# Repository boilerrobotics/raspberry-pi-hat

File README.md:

# RaspberryPi-Hat

Please update this readme.
Please make a KiCAD project, then update the PROJECT_NAME at the top of the pcb_image.yaml (inside the .github/workflows folder)

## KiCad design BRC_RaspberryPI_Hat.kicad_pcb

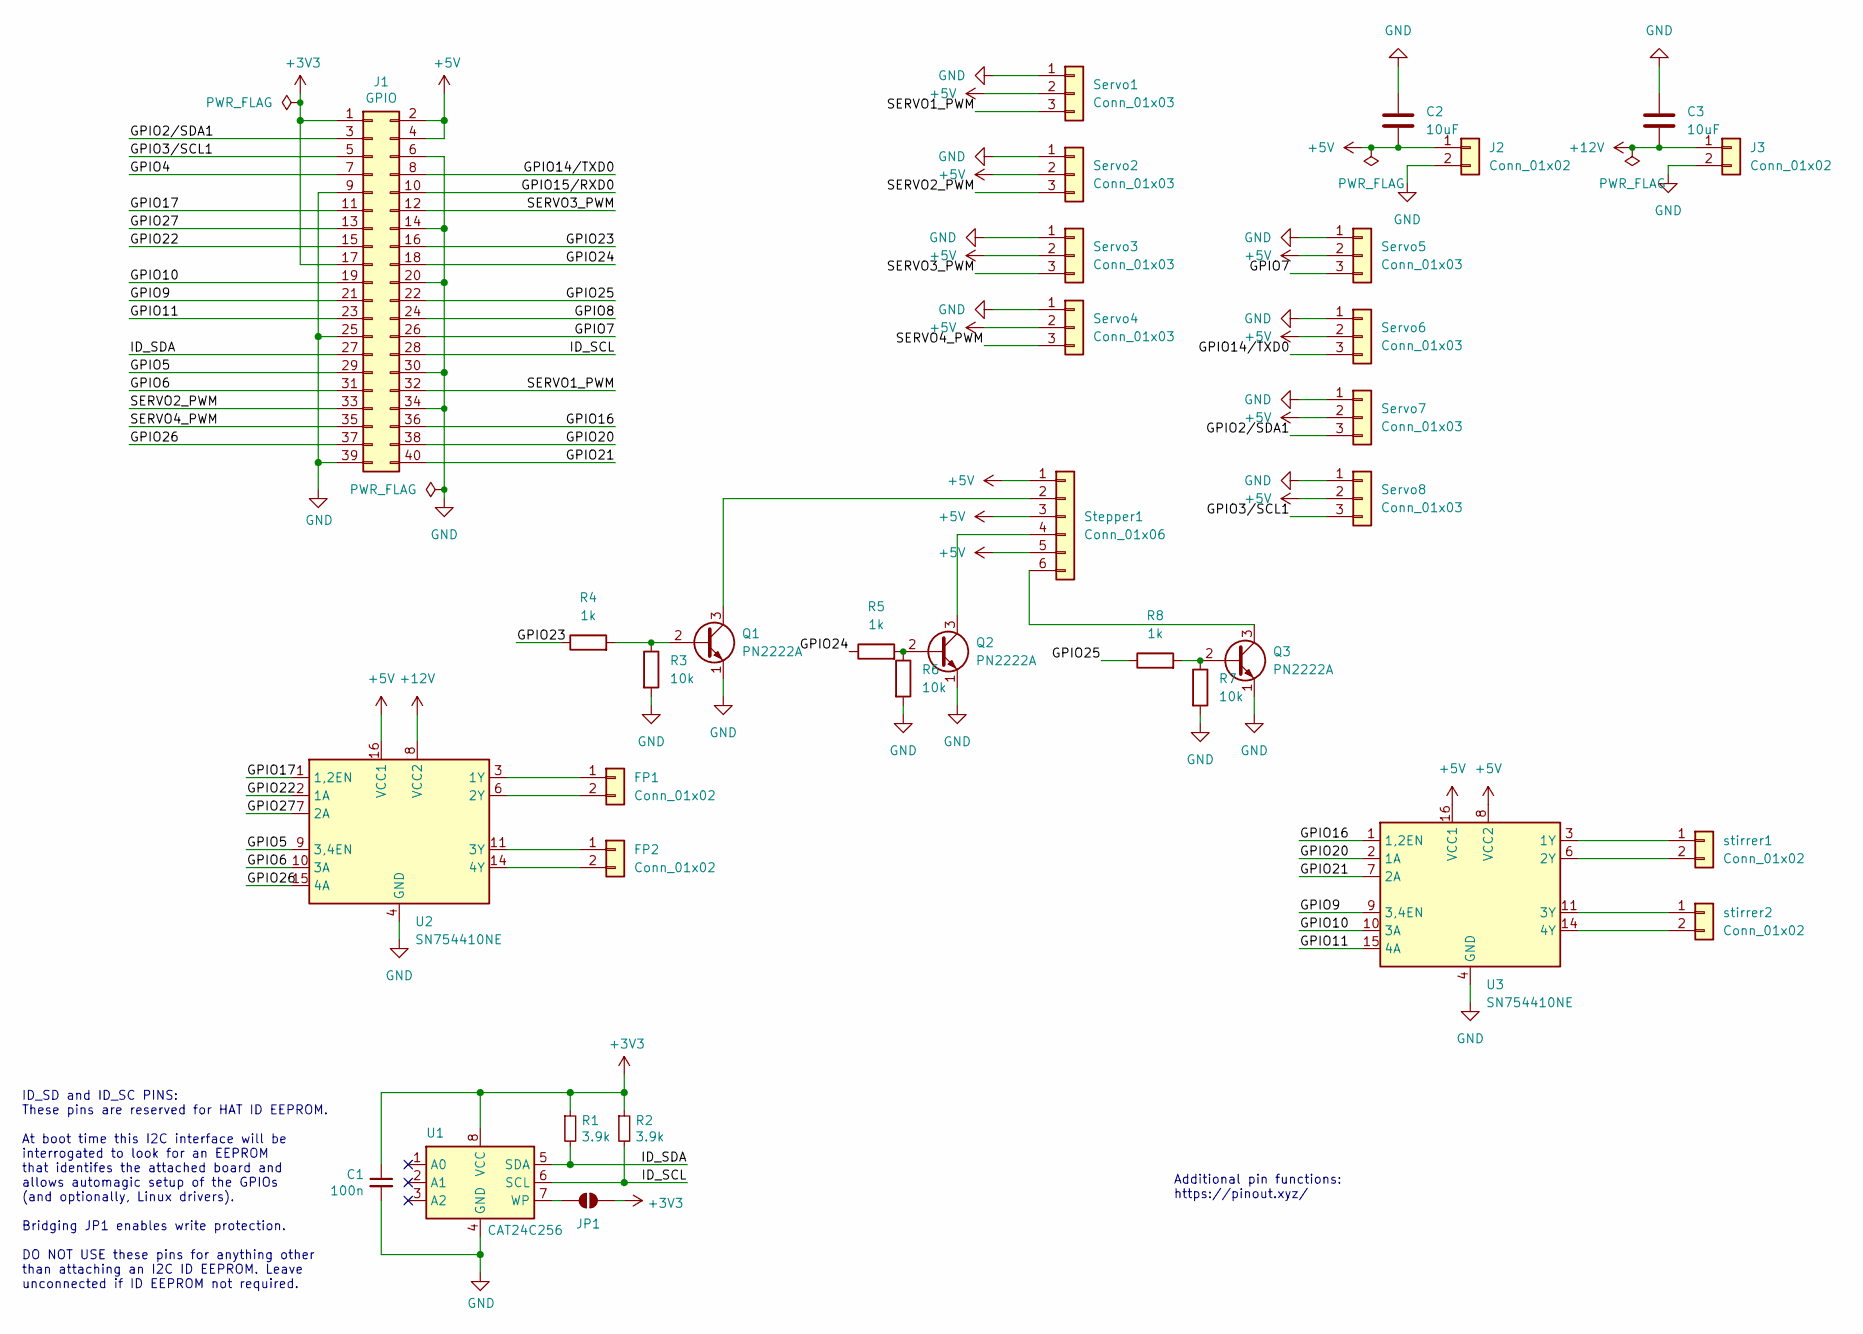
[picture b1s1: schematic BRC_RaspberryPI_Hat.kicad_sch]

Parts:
C1: 100n; C_Disc_D5.0mm_W2.5mm_P2.50mm
C2, C3: 10uF; C_0805_2012Metric
FP1, FP2: Conn_01x02; JST_XH_B2B-XH-A_1x02_P2.50mm_Vertical
J1: GPIO; PinSocket_2x20_P2.54mm_Vertical
J2, J3: Conn_01x02; AMASS_XT60-F_1x02_P7.20mm_Vertical
JP1: ID_WP
Q1, Q2, Q3: PN2222A; TO-92_Inline
R1, R2: 3.9k; R_Axial_DIN0207_L6.3mm_D2.5mm_P7.62mm_Horizontal
R3, R6, R7: 10k; R_Axial_DIN0207_L6.3mm_D2.5mm_P7.62mm_Horizontal
R4, R5, R8: 1k; R_Axial_DIN0207_L6.3mm_D2.5mm_P7.62mm_Horizontal
Servo1, Servo2, Servo3, Servo4, Servo5, Servo6, Servo7, Servo8: Conn_01x03; PinHeader_1x03_P2.54mm_Vertical
Stepper1: Conn_01x06; PinHeader_1x06_P2.54mm_Vertical
U1: CAT24C256
U2, U3: SN754410NE; DIP-16_W7.62mm
stirrer1, stirrer2: Conn_01x02; PinHeader_1x02_P2.54mm_Vertical

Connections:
+3V3: C1.1, J1.1, J1.17, JP1.2 (B), R1.1, R2.1, U1.8 (VCC)
+5V: C2.2, J1.2, J1.4, J2.1, Servo1.2, Servo2.2, Servo3.2, Servo4.2, Servo5.2, Servo6.2, Servo7.2, Servo8.2, Stepper1.1, Stepper1.3, Stepper1.5, U2.16 (VCC1), U3.8 (VCC2), U3.16 (VCC1)
+12V: C3.2, J3.1, U2.8 (VCC2)
/GPIO2/SDA1: J1.3, Servo7.3
/GPIO3/SCL1: J1.5, Servo8.3
/GPIO4: J1.7
/GPIO5: J1.29, U2.9 (3,4EN)
/GPIO6: J1.31, U2.10 (3A)
/GPIO7: J1.26, Servo5.3
/GPIO8: J1.24
/GPIO9: J1.21, U3.9 (3,4EN)
/GPIO10: J1.19, U3.10 (3A)
/GPIO11: J1.23, U3.15 (4A)
/GPIO14/TXD0: J1.8, Servo6.3
/GPIO15/RXD0: J1.10
/GPIO16: J1.36, U3.1 (1,2EN)
/GPIO17: J1.11, U2.1 (1,2EN)
/GPIO20: J1.38, U3.2 (1A)
/GPIO21: J1.40, U3.7 (2A)
/GPIO22: J1.15, U2.2 (1A)
/GPIO23: J1.16, R4.1
/GPIO24: J1.18, R5.1
/GPIO25: J1.22, R8.1
/GPIO26: J1.37, U2.15 (4A)
/GPIO27: J1.13, U2.7 (2A)
/ID_SCL: J1.28, R2.2, U1.6 (SCL)
/ID_SDA: J1.27, R1.2, U1.5 (SDA)
/SERVO1_PWM: J1.32, Servo1.3
/SERVO2_PWM: J1.33, Servo2.3
/SERVO3_PWM: J1.12, Servo3.3
/SERVO4_PWM: J1.35, Servo4.3
GND: C1.2, C2.1, C3.1, J1.6, J1.9, J1.14, J1.20, J1.25, J1.30, J1.34, J1.39, J2.2, J3.2, Q1.1 (E), Q2.1 (E), Q3.1 (E), R3.2, R6.2, R7.2, Servo1.1, Servo2.1, Servo3.1, Servo4.1, Servo5.1, Servo6.1, Servo7.1, Servo8.1, U1.4 (GND), U2.4 (GND), U2.5 (GND), U2.12 (GND), U2.13 (GND), U3.4 (GND), U3.5 (GND), U3.12 (GND), U3.13 (GND)
unnamed: FP1.1, U2.3 (1Y)
unnamed: FP1.2, U2.6 (2Y)
unnamed: FP2.1, U2.11 (3Y)
unnamed: FP2.2, U2.14 (4Y)
unnamed: JP1.1 (A), U1.7 (WP)
unnamed: Q1.2 (B), R3.1, R4.2
unnamed: Q1.3 (C), Stepper1.2
unnamed: Q2.2 (B), R5.2, R6.1
unnamed: Q2.3 (C), Stepper1.4
unnamed: Q3.2 (B), R7.1, R8.2
unnamed: Q3.3 (C), Stepper1.6
unnamed: U3.3 (1Y), stirrer1.1
unnamed: U3.6 (2Y), stirrer1.2
unnamed: U3.11 (3Y), stirrer2.1
unnamed: U3.14 (4Y), stirrer2.2

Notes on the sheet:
Additional pin functions: https://pinout.xyz/
ID_SD and ID_SC PINS: These pins are reserved for HAT ID EEPROM. At boot time this I2C interface will be interrogated to look for an EEPROM that identifes the attached board and allows automagic setup of the GPIOs (and optionally, Linux drivers). Bridging JP1 enables write protection. DO NOT USE th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

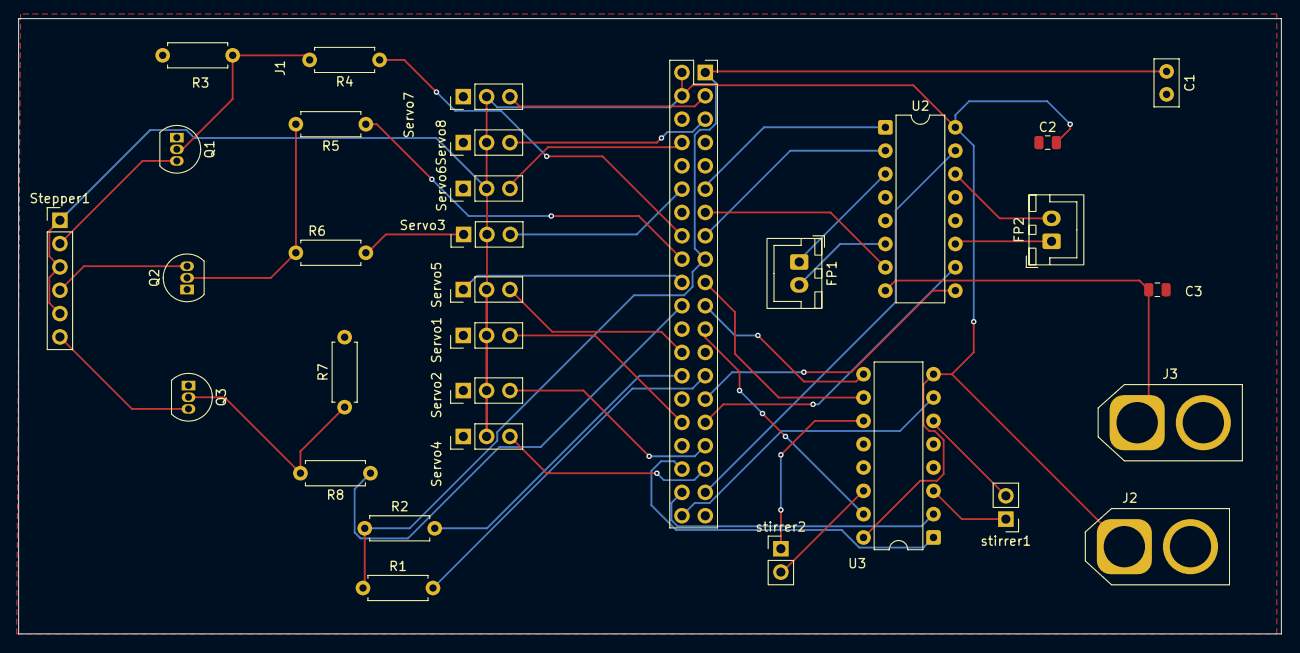
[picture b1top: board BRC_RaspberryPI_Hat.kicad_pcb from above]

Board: 2 copper layers, 137.5 x 67.0 mm, 32 parts (0 on the bottom side), 43 nets.
